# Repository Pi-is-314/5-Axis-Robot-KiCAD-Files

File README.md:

# 5-Axis-Robot-KiCAD-Files
KiCAD files for 5-axis Robot

WORK IN PROGRESS

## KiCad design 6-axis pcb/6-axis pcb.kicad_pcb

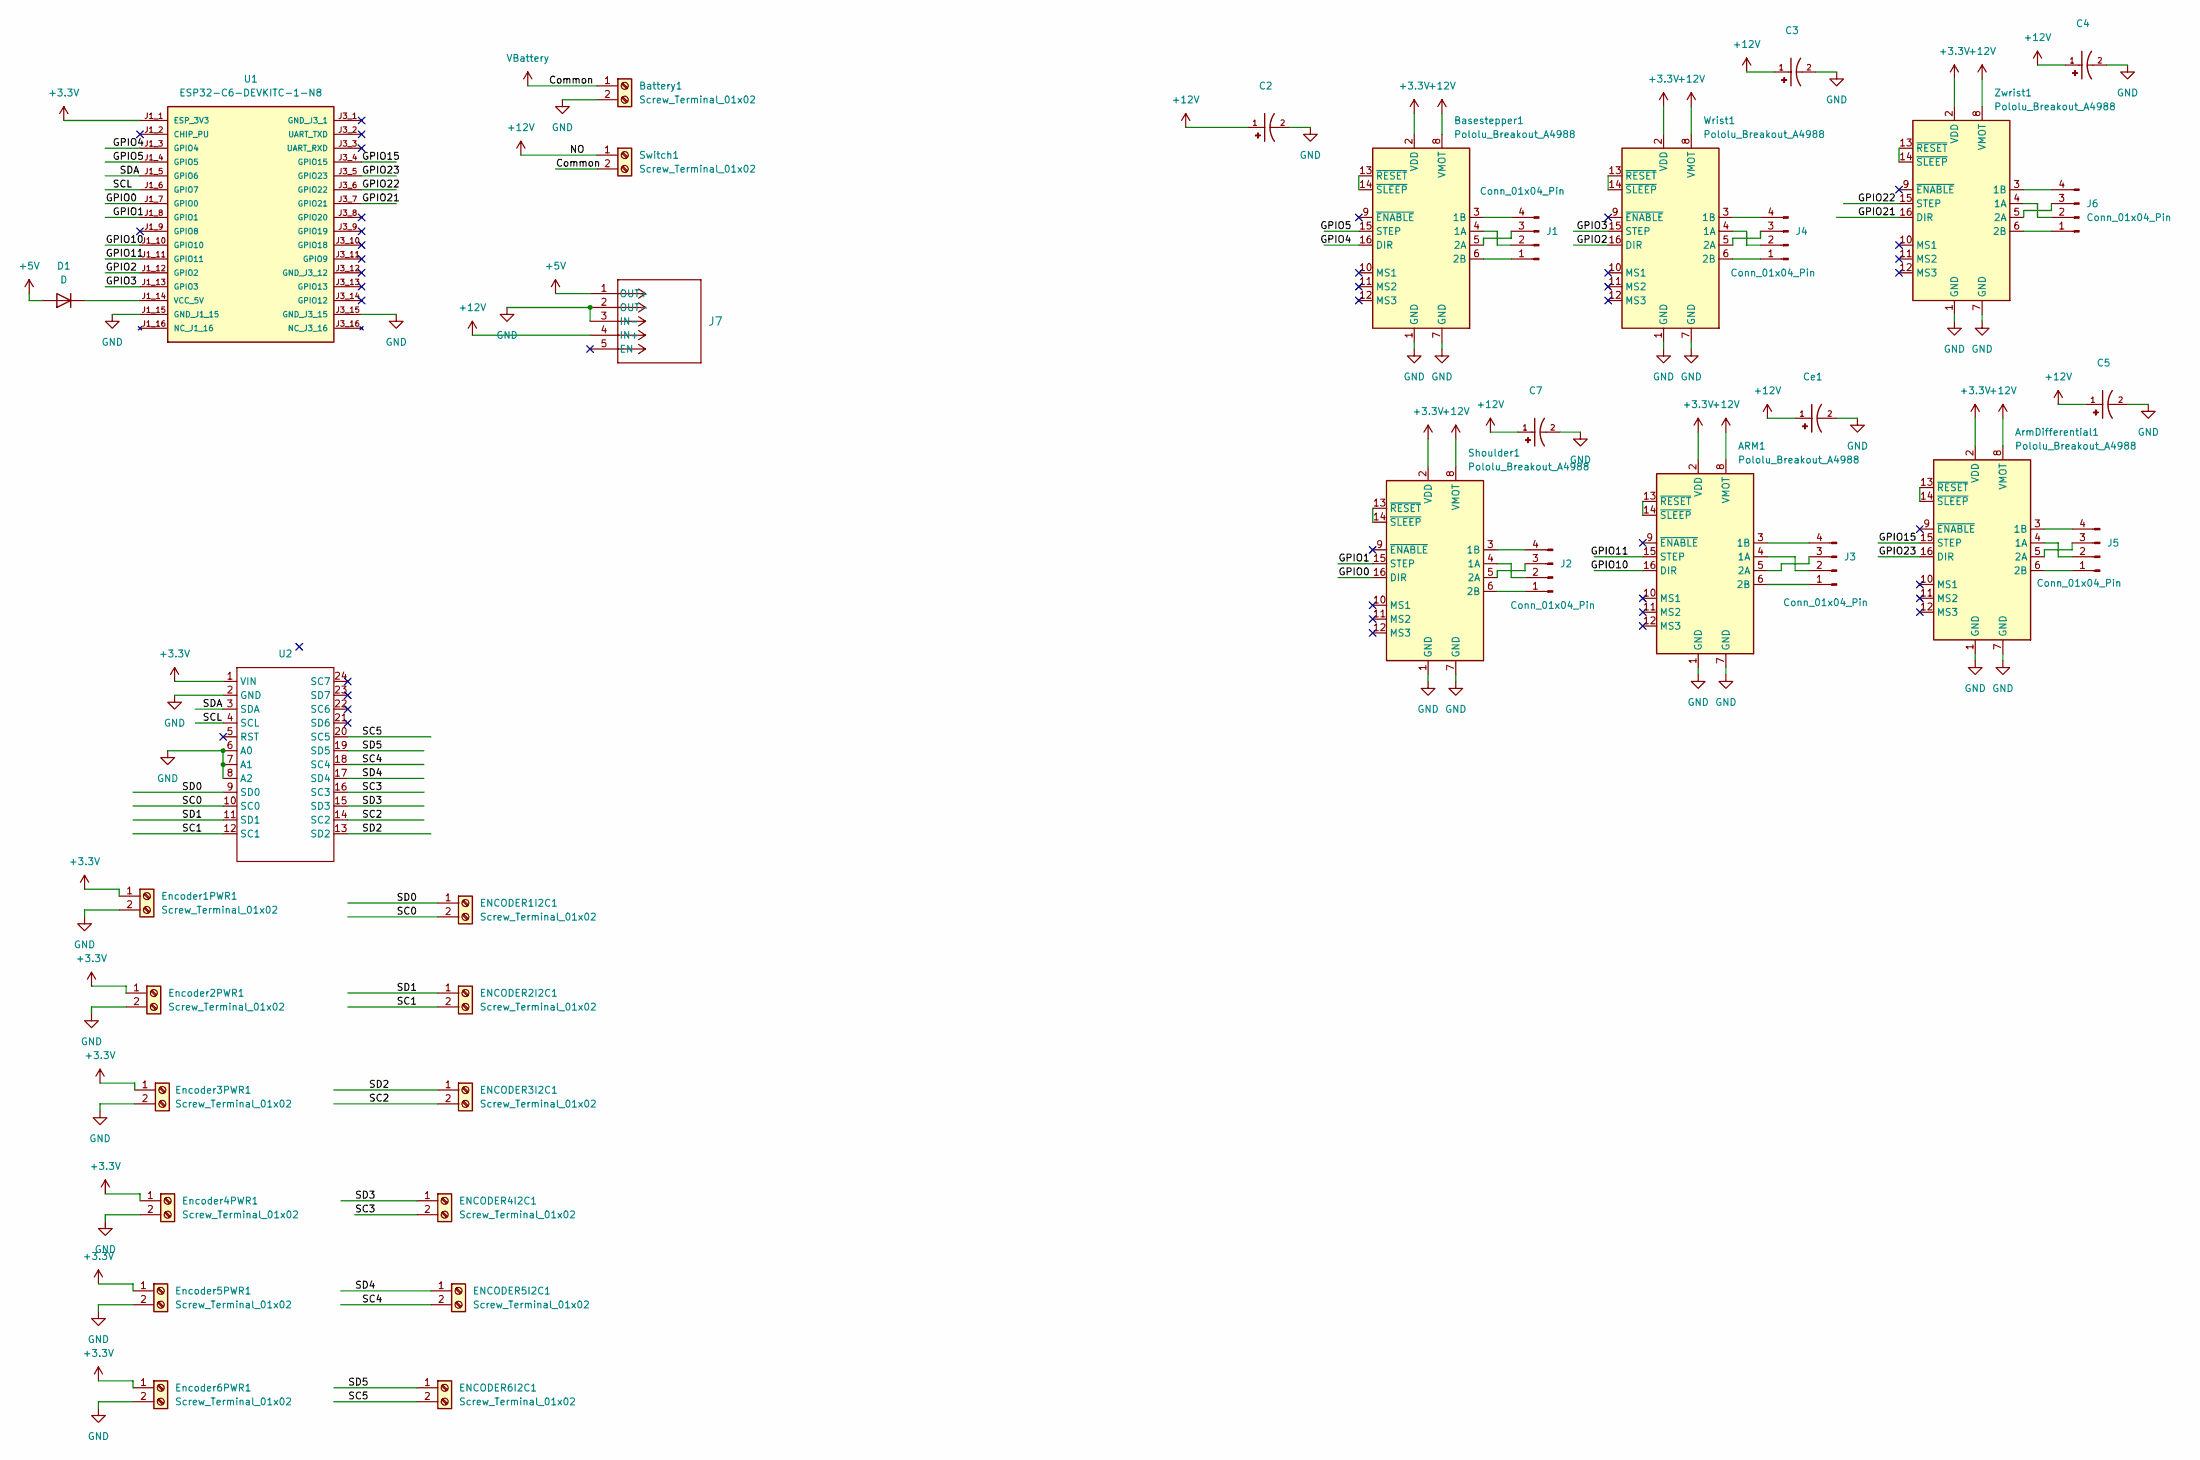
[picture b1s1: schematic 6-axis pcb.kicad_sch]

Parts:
ARM1: Pololu_Breakout_A4988; Pololu_Breakout-16_15.2x20.3mm
ArmDifferential1: Pololu_Breakout_A4988; Pololu_Breakout-16_15.2x20.3mm
Basestepper1: Pololu_Breakout_A4988; Pololu_Breakout-16_15.2x20.3mm
Battery1: Screw_Terminal_01x02; TerminalBlock_MaiXu_MX126-5.0-02P_1x02_P5.00mm
C2, C3, C4, C5, C7: EEUFK1V102S; CP_Radial_Tantal_D6.0mm_P2.50mm; PARTREV 20-DEC-19
Ce1: EEUFK1V102S; CP_Radial_Tantal_D6.0mm_P2.50mm; PARTREV 20-DEC-19
D1: D; D_5KPW_P12.70mm_Horizontal
ENCODER1I2C1, ENCODER2I2C1, ENCODER3I2C1, ENCODER4I2C1, ENCODER5I2C1, ENCODER6I2C1: Screw_Terminal_01x02; TerminalBlock_MaiXu_MX126-5.0-02P_1x02_P5.00mm
Encoder1PWR1, Encoder2PWR1, Encoder3PWR1, Encoder4PWR1, Encoder5PWR1, Encoder6PWR1: Screw_Terminal_01x02; TerminalBlock_MaiXu_MX126-5.0-02P_1x02_P5.00mm
J1, J2, J3, J4, J5, J6: Conn_01x04_Pin; PinSocket_1x04_P2.00mm_Vertical
J7: PinSocket_1x05_P2.54mm_Vertical
Shoulder1: Pololu_Breakout_A4988; Pololu_Breakout-16_15.2x20.3mm
Switch1: Screw_Terminal_01x02; TerminalBlock_MaiXu_MX126-5.0-02P_1x02_P5.00mm
U1: ESP32-C6-DEVKITC-1-N8; MODULE_ESP32-C6-DEVKITC-1-N8; PARTREV 1.3
U2: Untitled
Wrist1: Pololu_Breakout_A4988; Pololu_Breakout-16_15.2x20.3mm
Zwrist1: Pololu_Breakout_A4988; Pololu_Breakout-16_15.2x20.3mm

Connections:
+3.3V: ARM1.2 (VDD), ArmDifferential1.2 (VDD), Basestepper1.2 (VDD), Encoder1PWR1.1, Encoder2PWR1.1, Encoder3PWR1.1, Encoder4PWR1.1, Encoder5PWR1.1, Encoder6PWR1.1, Shoulder1.2 (VDD), U1.J1_1 (ESP_3V3), U2.1 (VIN), Wrist1.2 (VDD), Zwrist1.2 (VDD); also elsewhere on the board
+5V: D1.2 (A), J7.1 (OUT+)
+12V: ARM1.8 (VMOT), ArmDifferential1.8 (VMOT), Basestepper1.8 (VMOT), C2.1, C3.1, C4.1, C5.1, C7.1, Ce1.1, J7.4 (IN+), Shoulder1.8 (VMOT), Switch1.1, Wrist1.8 (VMOT), Zwrist1.8 (VMOT)
/GPIO0: Shoulder1.16 (DIR), U1.J1_7 (GPIO0)
/GPIO1: Shoulder1.15 (STEP), U1.J1_8 (GPIO1)
/GPIO2: U1.J1_12 (GPIO2), Wrist1.16 (DIR)
/GPIO3: U1.J1_13 (GPIO3), Wrist1.15 (STEP)
/GPIO4: Basestepper1.16 (DIR), U1.J1_3 (GPIO4)
/GPIO5: Basestepper1.15 (STEP), U1.J1_4 (GPIO5)
/GPIO10: ARM1.16 (DIR), U1.J1_10 (GPIO10)
/GPIO11: ARM1.15 (STEP), U1.J1_11 (GPIO11)
/GPIO15: ArmDifferential1.15 (STEP), U1.J3_4 (GPIO15)
/GPIO21: U1.J3_7 (GPIO21), Zwrist1.16 (DIR)
/GPIO22: U1.J3_6 (GPIO22), Zwrist1.15 (STEP)
/GPIO23: ArmDifferential1.16 (DIR), U1.J3_5 (GPIO23)
/SC0: ENCODER1I2C1.2, U2.10 (SC0); also elsewhere on the board
/SC1: ENCODER2I2C1.2, U2.12 (SC1); also elsewhere on the board
/SC2: ENCODER3I2C1.2, U2.14 (SC2); also elsewhere on the board
/SC3: ENCODER4I2C1.2, U2.16 (SC3); also elsewhere on the board
/SC4: ENCODER5I2C1.2, U2.18 (SC4); also elsewhere on the board
/SC5: ENCODER6I2C1.2, U2.20 (SC5); also elsewhere on the board
/SCL: U1.J1_6 (GPIO7), U2.4 (SCL); also elsewhere on the board
/SD0: ENCODER1I2C1.1, U2.9 (SD0); also elsewhere on the board
/SD1: ENCODER2I2C1.1, U2.11 (SD1); also elsewhere on the board
/SD2: ENCODER3I2C1.1, U2.13 (SD2); also elsewhere on the board
/SD3: ENCODER4I2C1.1, U2.15 (SD3); also elsewhere on the board
/SD4: ENCODER5I2C1.1, U2.17 (SD4); also elsewhere on the board
/SD5: ENCODER6I2C1.1, U2.19 (SD5); also elsewhere on the board
/SDA: U1.J1_5 (GPIO6), U2.3 (SDA); also elsewhere on the board
GND: ARM1.1 (GND), ARM1.7 (GND), ArmDifferential1.1 (GND), ArmDifferential1.7 (GND), Basestepper1.1 (GND), Basestepper1.7 (GND), Battery1.2, C2.2, C3.2, C4.2, C5.2, C7.2, Ce1.2, Encoder1PWR1.2, Encoder2PWR1.2, Encoder3PWR1.2, Encoder4PWR1.2, Encoder5PWR1.2, Encoder6PWR1.2, J7.2 (OUT-), J7.3 (IN-), Shoulder1.1 (GND), Shoulder1.7 (GND), U1.J1_15 (GND_J1_15), U1.J3_15 (GND_J3_15), U2.2 (GND), U2.6 (A0), U2.7 (A1), U2.8 (A2), Wrist1.1 (GND), Wrist1.7 (GND), Zwrist1.1 (GND), Zwrist1.7 (GND); also elsewhere on the board
unnamed: ARM1.4 (1A), J3.2
unnamed: ARM1.3 (1B), J3.4
unnamed: ARM1.5 (2A), J3.3
unnamed: ARM1.6 (2B), J3.1
unnamed: ARM1.13 (~RESET), ARM1.14 (~SLEEP)
unnamed: ArmDifferential1.4 (1A), J5.2
unnamed: ArmDifferential1.3 (1B), J5.4
unnamed: ArmDifferential1.5 (2A), J5.3
unnamed: ArmDifferential1.6 (2B), J5.1
unnamed: ArmDifferential1.13 (~RESET), ArmDifferential1.14 (~SLEEP)
unnamed: Basestepper1.4 (1A), J1.2
unnamed: Basestepper1.3 (1B), J1.4
unnamed: Basestepper1.5 (2A), J1.3
unnamed: Basestepper1.6 (2B), J1.1
unnamed: Basestepper1.13 (~RESET), Basestepper1.14 (~SLEEP)
unnamed: D1.1 (K), U1.J1_14 (VCC_5V)
unnamed: J2.1, Shoulder1.6 (2B)
unnamed: J2.2, Shoulder1.4 (1A)
unnamed: J2.3, Shoulder1.5 (2A)
unnamed: J2.4, Shoulder1.3 (1B)
unnamed: J4.1, Wrist1.6 (2B)
unnamed: J4.2, Wrist1.4 (1A)
unnamed: J4.3, Wrist1.5 (2A)
unnamed: J4.4, Wrist1.3 (1B)
unnamed: J6.1, Zwrist1.6 (2B)
unnamed: J6.2, Zwrist1.4 (1A)
unnamed: J6.3, Zwrist1.5 (2A)
unnamed: J6.4, Zwrist1.3 (1B)
unnamed: Shoulder1.13 (~RESET), Shoulder1.14 (~SLEEP)
unnamed: Wrist1.13 (~RESET), Wrist1.14 (~SLEEP)
unnamed: Zwrist1.13 (~RESET), Zwrist1.14 (~SLEEP)
VBattery: Battery1.1, Switch1.2

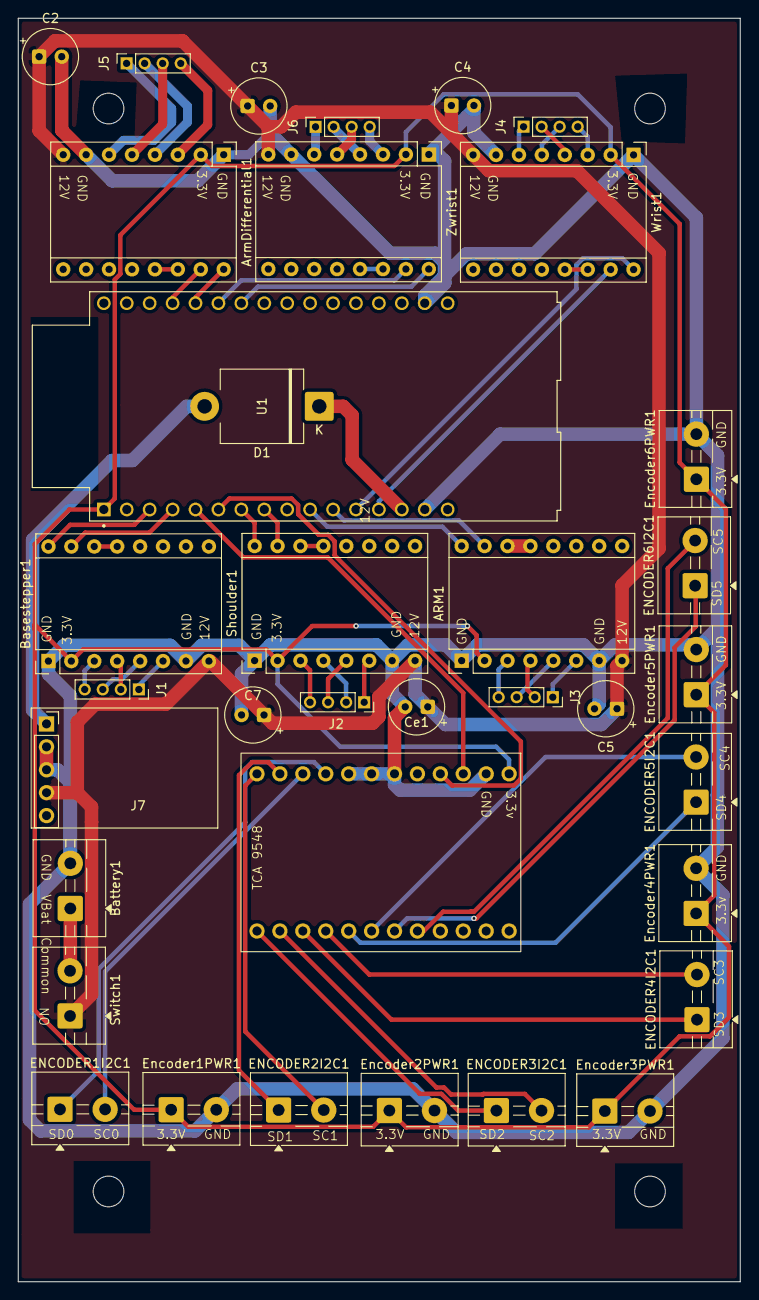
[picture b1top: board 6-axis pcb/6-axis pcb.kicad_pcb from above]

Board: 2 copper layers, 80.0 x 140.0 mm, 36 parts (0 on the bottom side), 62 nets.

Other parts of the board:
TCA 9548: Untitled

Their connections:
+3.3V: TCA 9548.1 (VIN); also elsewhere on the board
/SC0: TCA 9548.10 (SC0); also elsewhere on the board
/SC1: TCA 9548.12 (SC1); also elsewhere on the board
/SC2: TCA 9548.14 (SC2); also elsewhere on the board
/SC3: TCA 9548.16 (SC3); also elsewhere on the board
/SC4: TCA 9548.18 (SC4); also elsewhere on the board
/SC5: TCA 9548.20 (SC5); also elsewhere on the board
/SCL: TCA 9548.4 (SCL); also elsewhere on the board
/SD0: TCA 9548.9 (SD0); also elsewhere on the board
/SD1: TCA 9548.11 (SD1); also elsewhere on the board
/SD2: TCA 9548.13 (SD2); also elsewhere on the board
/SD3: TCA 9548.15 (SD3); also elsewhere on the board
/SD4: TCA 9548.17 (SD4); also elsewhere on the board
/SD5: TCA 9548.19 (SD5); also elsewhere on the board
/SDA: TCA 9548.3 (SDA); also elsewhere on the board
GND: TCA 9548.2 (GND), TCA 9548.6 (A0), TCA 9548.7 (A1), TCA 9548.8 (A2); also elsewhere on the board

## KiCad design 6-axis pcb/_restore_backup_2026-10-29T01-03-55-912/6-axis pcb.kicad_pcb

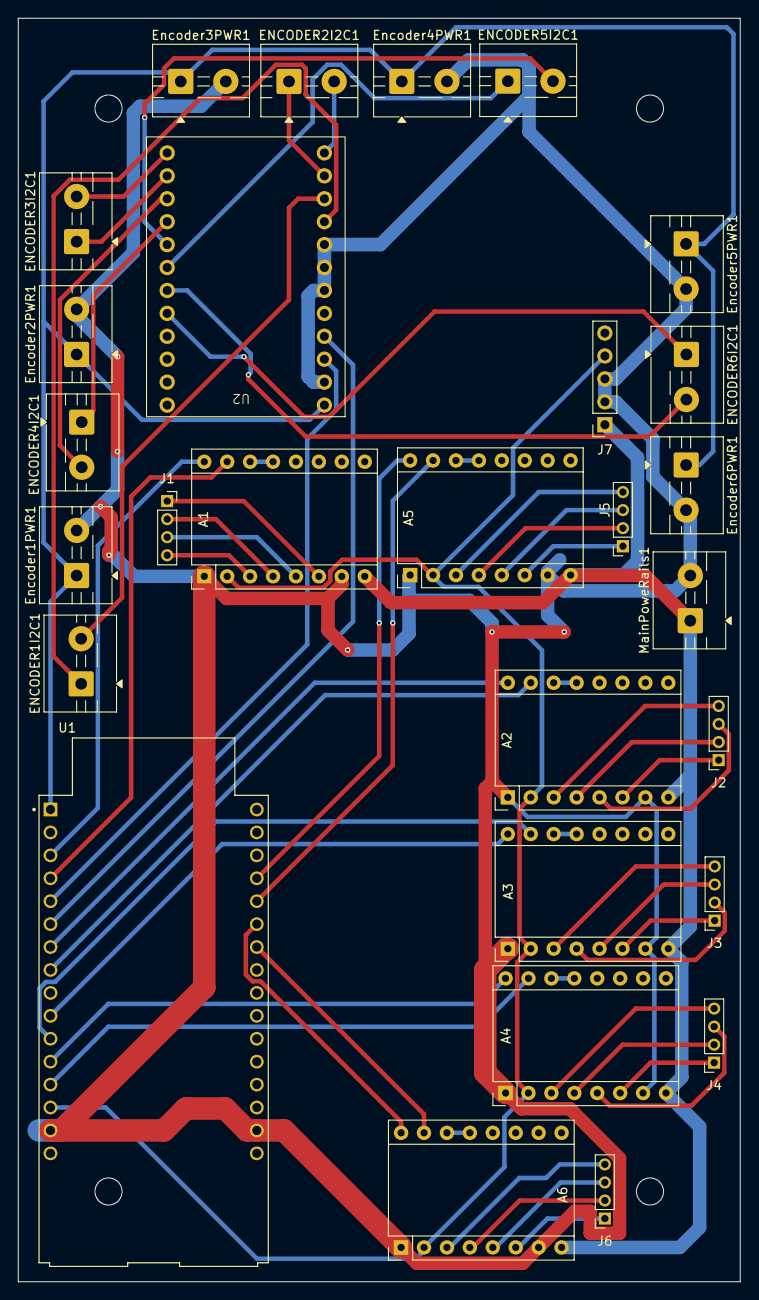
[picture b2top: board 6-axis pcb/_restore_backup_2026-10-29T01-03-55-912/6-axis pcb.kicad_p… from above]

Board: 2 copper layers, 80.0 x 140.0 mm, 28 parts (0 on the bottom side), 60 nets.

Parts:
A1, A2, A3, A4, A5, A6: Pololu_Breakout_A4988; Pololu_Breakout-16_15.2x20.3mm
ENCODER1I2C1, ENCODER2I2C1, ENCODER3I2C1, ENCODER4I2C1, ENCODER5I2C1, ENCODER6I2C1: Screw_Terminal_01x02; TerminalBlock_MaiXu_MX126-5.0-02P_1x02_P5.00mm
Encoder1PWR1, Encoder2PWR1, Encoder3PWR1, Encoder4PWR1, Encoder5PWR1, Encoder6PWR1: Screw_Terminal_01x02; TerminalBlock_MaiXu_MX126-5.0-02P_1x02_P5.00mm
J1, J2, J3, J4, J5, J6: Conn_01x04_Pin; PinSocket_1x04_P2.00mm_Vertical
J7: PinSocket_1x05_P2.54mm_Vertical
MainPoweRails1: Screw_Terminal_01x02; TerminalBlock_MaiXu_MX126-5.0-02P_1x02_P5.00mm
U1: ESP32-C6-DEVKITC-1-N8; MODULE_ESP32-C6-DEVKITC-1-N8
U2: Untitled

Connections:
+3.3V: Encoder1PWR1.1, Encoder2PWR1.1, Encoder3PWR1.1, Encoder4PWR1.1, Encoder5PWR1.1, Encoder6PWR1.1, U1.J1_1 (ESP_3V3), U2.1 (VIN)
+5V: A1.2 (VDD), A2.2 (VDD), A3.2 (VDD), A4.2 (VDD), A5.2 (VDD), A6.2 (VDD), J7.4 (IN+), U1.J1_14 (VCC_5V)
+12V: A1.8 (VMOT), A2.8 (VMOT), A3.8 (VMOT), A4.8 (VMOT), A5.8 (VMOT), A6.8 (VMOT), J7.1 (OUT+), MainPoweRails1.1
/<NO NET>: ENCODER5I2C1.2, U2.17 (SD4)
/GPIO0: A2.16 (DIR), U1.J1_7 (GPIO0)
/GPIO1: A2.15 (STEP), U1.J1_8 (GPIO1)
/GPIO2: A4.16 (DIR), U1.J1_12 (GPIO2)
/GPIO3: A4.15 (STEP), U1.J1_13 (GPIO3)
/GPIO4: A1.16 (DIR), U1.J1_3 (GPIO4)
/GPIO5: A1.15 (STEP), U1.J1_4 (GPIO5)
/GPIO10: A3.16 (DIR), U1.J1_10 (GPIO10)
/GPIO11: A3.15 (STEP), U1.J1_11 (GPIO11)
/GPIO15: A5.16 (DIR), U1.J3_4 (GPIO15)
/GPIO21: A6.15 (STEP), U1.J3_7 (GPIO21)
/GPIO22: A6.16 (DIR), U1.J3_6 (GPIO22)
/GPIO23: A5.15 (STEP), U1.J3_5 (GPIO23)
/SC0: ENCODER1I2C1.2, U2.10 (SC0)
/SC1: ENCODER2I2C1.2, U2.12 (SC1)
/SC2: ENCODER3I2C1.1, U2.14 (SC2)
/SC3: ENCODER4I2C1.1, U2.16 (SC3)
/SC4: ENCODER5I2C1.1, U2.18 (SC4)
/SC5: ENCODER6I2C1.1, U2.20 (SC5)
/SCL: U1.J1_6 (GPIO7), U2.4 (SCL)
/SD0: ENCODER1I2C1.1, U2.9 (SD0)
/SD1: ENCODER2I2C1.1, U2.11 (SD1)
/SD2: ENCODER3I2C1.2, U2.13 (SD2)
/SD3: ENCODER4I2C1.2, U2.15 (SD3)
/SD5: ENCODER6I2C1.2, U2.19 (SD5)
/SDA: U1.J1_5 (GPIO6), U2.3 (SDA)
GND: A1.1 (GND), A1.7 (GND), A2.1 (GND), A2.7 (GND), A3.1 (GND), A3.7 (GND), A4.1 (GND), A4.7 (GND), A5.1 (GND), A5.7 (GND), A6.1 (GND), A6.7 (GND), Encoder1PWR1.2, Encoder2PWR1.2, Encoder3PWR1.2, Encoder4PWR1.2, Encoder5PWR1.2, Encoder6PWR1.2, J7.2 (OUT-), J7.3 (IN-), MainPoweRails1.2, U1.J1_15 (GND_J1_15), U1.J3_15 (GND_J3_15), U2.2 (GND), U2.6 (A0), U2.7 (A1), U2.8 (A2)
unnamed: A1.4 (1A), J1.2
unnamed: A1.3 (1B), J1.4
unnamed: A1.5 (2A), J1.3
unnamed: A1.6 (2B), J1.1
unnamed: A1.13 (~RESET), A1.14 (~SLEEP)
unnamed: A2.4 (1A), J2.2
unnamed: A2.3 (1B), J2.4
unnamed: A2.5 (2A), J2.3
unnamed: A2.6 (2B), J2.1
unnamed: A2.13 (~RESET), A2.14 (~SLEEP)
unnamed: A3.4 (1A), J3.2
unnamed: A3.3 (1B), J3.4
unnamed: A3.5 (2A), J3.3
unnamed: A3.6 (2B), J3.1
unnamed: A3.13 (~RESET), A3.14 (~SLEEP)
unnamed: A4.4 (1A), J4.2
unnamed: A4.3 (1B), J4.4
unnamed: A4.5 (2A), J4.3
unnamed: A4.6 (2B), J4.1
unnamed: A4.13 (~RESET), A4.14 (~SLEEP)
unnamed: A5.4 (1A), J5.2
unnamed: A5.3 (1B), J5.4
unnamed: A5.5 (2A), J5.3
unnamed: A5.6 (2B), J5.1
unnamed: A5.13 (~RESET), A5.14 (~SLEEP)
unnamed: A6.4 (1A), J6.2
unnamed: A6.3 (1B), J6.4
unnamed: A6.5 (2A), J6.3
unnamed: A6.6 (2B), J6.1
unnamed: A6.13 (~RESET), A6.14 (~SLEEP)
